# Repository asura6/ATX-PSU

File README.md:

# ATX-PSU
ATX Breakout PCB with current- and voltage monitoring using a STM32 microcontroller and a LCD screen.

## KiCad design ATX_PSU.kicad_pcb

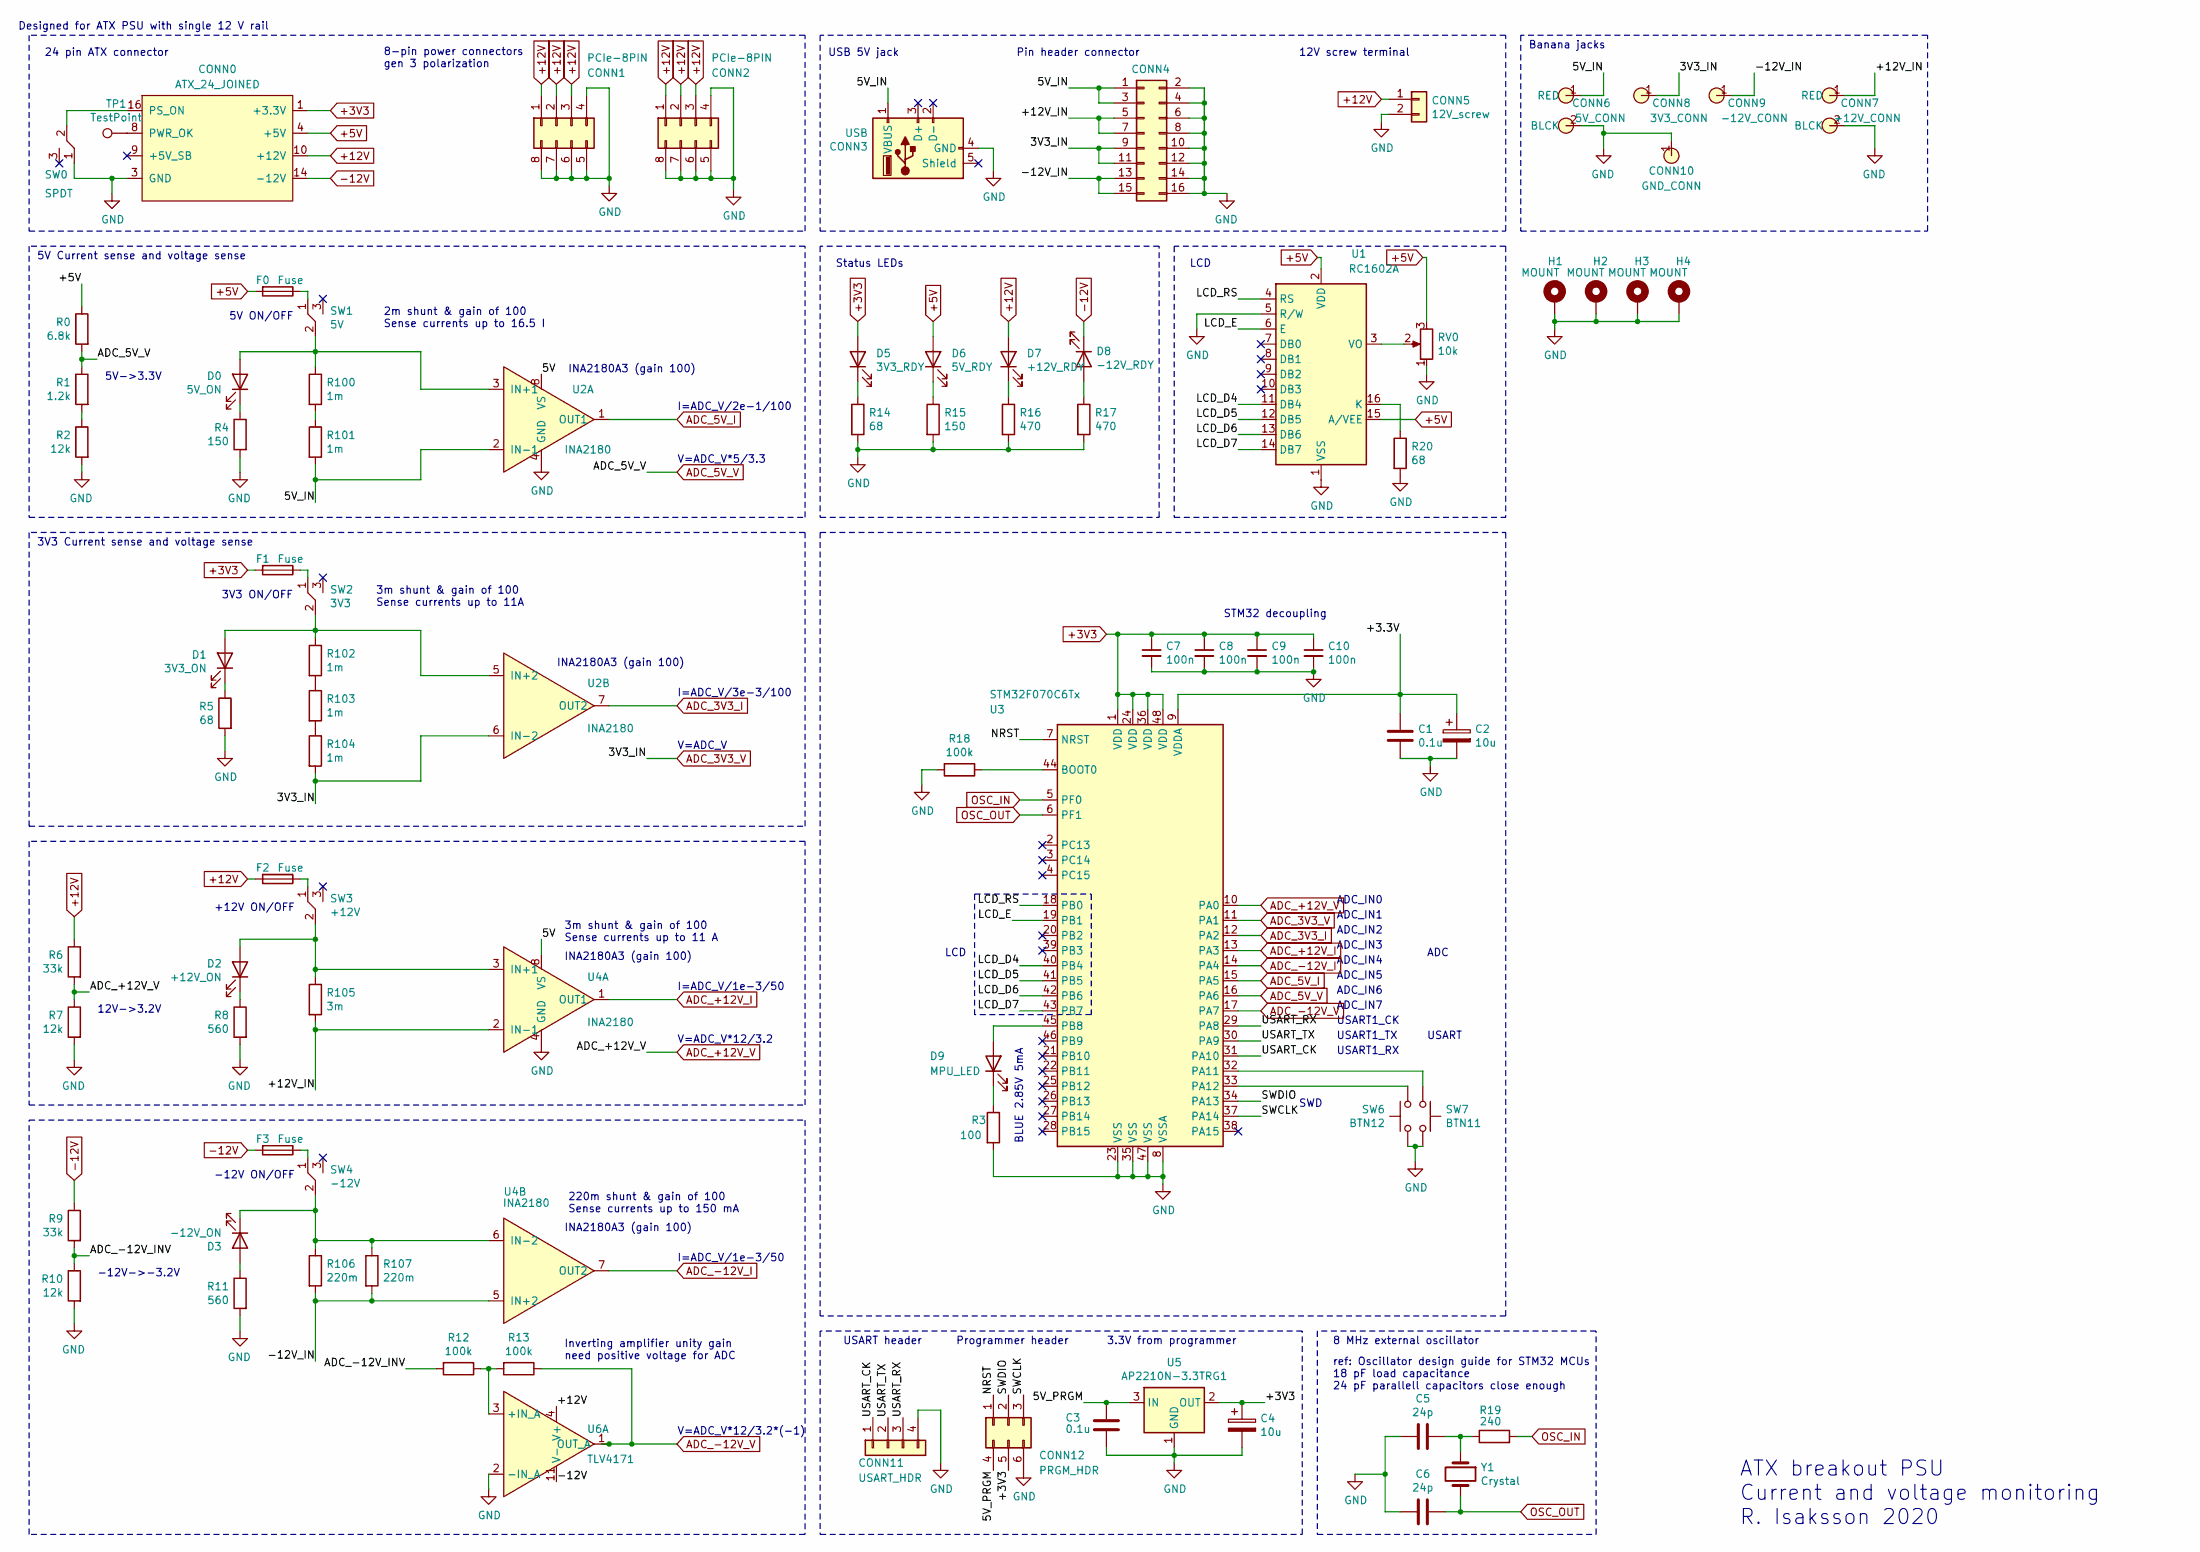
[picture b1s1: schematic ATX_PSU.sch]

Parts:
C1, C3: 0.1u; C_0603_1608Metric
C2, C4: 10u; CP_EIA-3528-12_Kemet-T
C5, C6: 24p; C_0603_1608Metric
C7, C8, C9, C10: 100n; C_0603_1608Metric
CONN0: ATX_24_JOINED; Molex_Mini-Fit_Jr_5569-24A2_2x12_P4.20mm_Horizontal
CONN1, CONN2: PCIe-8PIN; Molex_Mini-Fit_Jr_455860005_2x04_P4.20mm_Horizontal
CONN3: USB; USB_Micro-B_Molex_47346-0001
CONN4: Conn_02x08_Odd_Even; PinHeader_2x08_P2.54mm_Vertical
CONN5: 12V_screw; Phoenix_01x02_1935776
CONN6: 5V_CONN; 2x_BNNA
CONN7: +12V_CONN; 2x_BNNA
CONN8: 3V3_CONN; 1x_BNNA
CONN9: -12V_CONN; 1x_BNNA
CONN10: GND_CONN; 1x_BNNA
CONN11: USART_HDR; PinHeader_1x04_P2.54mm_Vertical
CONN12: PRGM_HDR; PinHeader_2x03_P2.54mm_Vertical
D0: 5V_ON; LED_1206_3216Metric
D1: 3V3_ON; LED_1206_3216Metric
D2: +12V_ON; LED_1206_3216Metric
D3: -12V_ON; LED_1206_3216Metric
D5: 3V3_RDY; LED_1206_3216Metric
D6: 5V_RDY; LED_1206_3216Metric
D7: +12V_RDY; LED_1206_3216Metric
D8: -12V_RDY; LED_1206_3216Metric
D9: MPU_LED; LED_0603_1608Metric
F0, F1, F2, F3: Fuse; Fuseholder_Cylinder-5x20mm_Stelvio-Kontek_PTF78_Horizontal_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
H1, H2, H3, H4: MOUNT; MountingHole_4.3mm_M4_Pad_Via
R0: 6.8k; R_0805_2012Metric
R1: 1.2k; R_0805_2012Metric
R2, R7, R10: 12k; R_0805_2012Metric
R3: 100; R_0805_2012Metric
R4, R15: 150; R_0805_2012Metric
R5, R14, R20: 68; R_0805_2012Metric
R6, R9: 33k; R_0805_2012Metric
R8, R11: 560; R_0805_2012Metric
R12, R13, R18: 100k; R_0805_2012Metric
R16, R17: 470; R_0805_2012Metric
R19: 240; R_0805_2012Metric
R100, R101, R102, R103, R104: 1m; R_2512_6332Metric
R105: 3m; R_1206_3216Metric
R106, R107: 220m; R_1206_3216Metric
RV0: 10k; 3361P
SW0: SPDT; RI_SPDT
SW1: 5V; RI_SPDT
SW2: 3V3; RI_SPDT
SW3: +12V; RI_SPDT
SW4: -12V; RI_SPDT
SW6: BTN12; SW_PUSH_6mm
SW7: BTN11; SW_PUSH_6mm
TP1: TestPoint; TestPoint_THTPad_2.5x2.5mm_Drill1.2mm
U1: RC1602A; LCD_4ROW
U2, U4: INA2180; VSSOP-8_3.0x3.0mm_P0.65mm
U3: STM32F070C6Tx; LQFP-48_7x7mm_P0.5mm
U5: AP2210N-3.3TRG1; SOT-23_Handsoldering
U6: TLV4171; SOIC-14_3.9x8.7mm_P1.27mm
Y1: Crystal; LFXTAL020423

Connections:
+3V3: C4.1, C7.1, C8.1, C9.1, C10.1, CONN0.1 (+3.3V), CONN0.2 (+3.3V), CONN0.12 (+3.3V), CONN0.13 (+3.3V), CONN12.5, D5.2 (A), F1.2, U3.1 (VDD), U3.24 (VDD), U3.36 (VDD), U3.48 (VDD), U5.2 (OUT)
+5V: CONN0.4 (+5V), CONN0.6 (+5V), CONN0.21 (+5V), CONN0.22 (+5V), CONN0.23 (+5V), D6.2 (A), F0.2, R0.1, RV0.3, U1.2 (VDD), U1.15 (A/VEE)
+12V: CONN0.10 (+12V), CONN0.11 (+12V), CONN1.1, CONN1.2, CONN1.3, CONN2.1, CONN2.2, CONN2.3, CONN5.1, D7.2 (A), F2.2, R6.1, U6.4 (V+)
-12V: CONN0.14 (-12V), D8.1 (K), F3.2, R9.1, U6.11 (V-)
/5V: U2.8 (VS), U4.8 (VS)
/5V_IN: CONN3.1 (VBUS), CONN4.1, CONN4.3, CONN6.1 (RED), R101.2, U2.2 (IN-1)
/5V_PRGM: C3.1, CONN12.4, U5.3 (IN)
/+3.3V: C1.1, C2.1, U3.9 (VDDA)
/+12V_IN: CONN4.5, CONN4.7, CONN7.1 (RED), R105.2, U4.2 (IN-1)
/-12V_IN: CONN4.13, CONN4.15, CONN9.1, R106.2, R107.2, U4.5 (IN+2)
/ADC_-12V_INV: R9.2, R10.1, R12.2
/LCD_D4: U1.11 (DB4), U3.40 (PB4)
/LCD_D5: U1.12 (DB5), U3.41 (PB5)
/LCD_D6: U1.13 (DB6), U3.42 (PB6)
/LCD_D7: U1.14 (DB7), U3.43 (PB7)
/LCD_E: U1.6 (E), U3.19 (PB1)
/LCD_RS: U1.4 (RS), U3.18 (PB0)
/NRST: CONN12.1, U3.7 (NRST)
/SWCLK: CONN12.3, U3.37 (PA14)
/SWDIO: CONN12.2, U3.34 (PA13)
/USART_CK: CONN11.1, U3.31 (PA10)
/USART_RX: CONN11.3, U3.29 (PA8)
/USART_TX: CONN11.2, U3.30 (PA9)
ADC_3V3_I: U2.7 (OUT2), U3.12 (PA2)
ADC_3V3_V: CONN4.9, CONN4.11, CONN8.1, R104.2, U2.6 (IN-2), U3.11 (PA1)
ADC_5V_I: U2.1 (OUT1), U3.15 (PA5)
ADC_5V_V: R0.2, R1.1, U3.16 (PA6)
ADC_+12V_I: U3.13 (PA3), U4.1 (OUT1)
ADC_+12V_V: R6.2, R7.1, U3.10 (PA0)
ADC_-12V_I: U3.14 (PA4), U4.7 (OUT2)
ADC_-12V_V: R13.1, U3.17 (PA7), U6.1 (OUT_A)
GND: C1.2, C2.2, C3.2, C4.2, C5.2, C6.2, C7.2, C8.2, C9.2, C10.2, CONN0.3 (GND), CONN0.5 (GND), CONN0.7 (GND), CONN0.15 (GND), CONN0.17 (GND), CONN0.18 (GND), CONN0.19 (GND), CONN0.24 (GND), CONN1.4, CONN1.5, CONN1.6, CONN1.7, CONN1.8, CONN2.4, CONN2.5, CONN2.6, CONN2.7, CONN2.8, CONN3.4 (GND), CONN4.2, CONN4.4, CONN4.6, CONN4.8, CONN4.10, CONN4.12, CONN4.14, CONN4.16, CONN5.2, CONN6.2 (BLCK), CONN7.2 (BLCK), CONN10.1, CONN11.4, CONN12.6, H1.1, H2.1, H3.1, H4.1, R2.2, R3.2, R4.2, R5.2, R7.2, R8.2, R10.2, R11.2, R14.2, R15.2, R16.2, R17.2, R18.2, R20.2, RV0.1, SW0.1, SW6.2, SW7.2, U1.1 (VSS), U1.5 (R/W), U2.4 (GND), U3.8 (VSSA), U3.23 (VSS), U3.35 (VSS), U3.47 (VSS), U4.4 (GND), U5.1 (GND), U6.2 (-IN_A)
unnamed: C5.1, R19.1, Y1.1
unnamed: CONN0.8 (PWR_OK), TP1.1
unnamed: CONN0.16 (PS_ON), SW0.2
unnamed: D0.1 (K), R4.1
unnamed: D0.2 (A), R100.1, SW1.2, U2.3 (IN+1)
unnamed: D1.1 (K), R5.1
unnamed: D1.2 (A), R102.1, SW2.2, U2.5 (IN+2)
unnamed: D2.1 (K), R8.1
unnamed: D2.2 (A), R105.1, SW3.2, U4.3 (IN+1)
unnamed: D3.1 (K), R106.1, R107.1, SW4.2, U4.6 (IN-2)
unnamed: D3.2 (A), R11.1
unnamed: D5.1 (K), R14.1
unnamed: D6.1 (K), R15.1
unnamed: D7.1 (K), R16.1
unnamed: D8.2 (A), R17.1
unnamed: D9.1 (K), R3.1
unnamed: D9.2 (A), U3.45 (PB8)
unnamed: F0.1, SW1.1
unnamed: F1.1, SW2.1
unnamed: F2.1, SW3.1
unnamed: F3.1, SW4.1
unnamed: R1.2, R2.1
unnamed: R12.1, R13.2, U6.3 (+IN_A)
unnamed: R18.1, U3.44 (BOOT0)
unnamed: R20.1, U1.16 (K)
unnamed: R100.2, R101.1
unnamed: R102.2, R103.1
unnamed: R103.2, R104.1
unnamed: RV0.2, U1.3 (VO)
unnamed: SW6.1, U3.33 (PA12)
unnamed: SW7.1, U3.32 (PA11)
OSC_IN: R19.2, U3.5 (PF0)
OSC_OUT: C6.1, U3.6 (PF1), Y1.2

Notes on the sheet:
24 pin ATX connector
Status LEDs
5V Current sense and voltage sense
3m shunt & gain of 100 Sense currents up to 11A
2m shunt & gain of 100 Sense currents up to 16.5 I
USB 5V jack
INA2180A3 (gain 100)
I=ADC_V/3e-3/100
V=ADC_V
I=ADC_V/2e-1/100
5V->3.3V
V=ADC_V*5/3.3
3V3 Current sense and voltage sense
12V->3.2V
V=ADC_V*12/3.2
I=ADC_V/1e-3/50
3m shunt & gain of 100 Sense currents up to 11 A
-12V->-3.2V
V=ADC_V*12/3.2*(-1)
220m shunt & gain of 100 Sense currents up to 150 mA
Inverting amplifier unity gain need positive voltage for ADC
Banana jacks
Pin header connector
Programmer header
8 MHz external oscillator
ref: Oscillator design guide for STM32 MCUs 18 pF load capacitance 24 pF parallell capacitors close enough
3.3V from programmer
ADC_IN0
ADC_IN1
ADC_IN2
ADC_IN3
ADC_IN4
ADC_IN5
ADC_IN6
ADC_IN7
USART1_CK
USART1_TX
USART1_RX
USART header
ADC

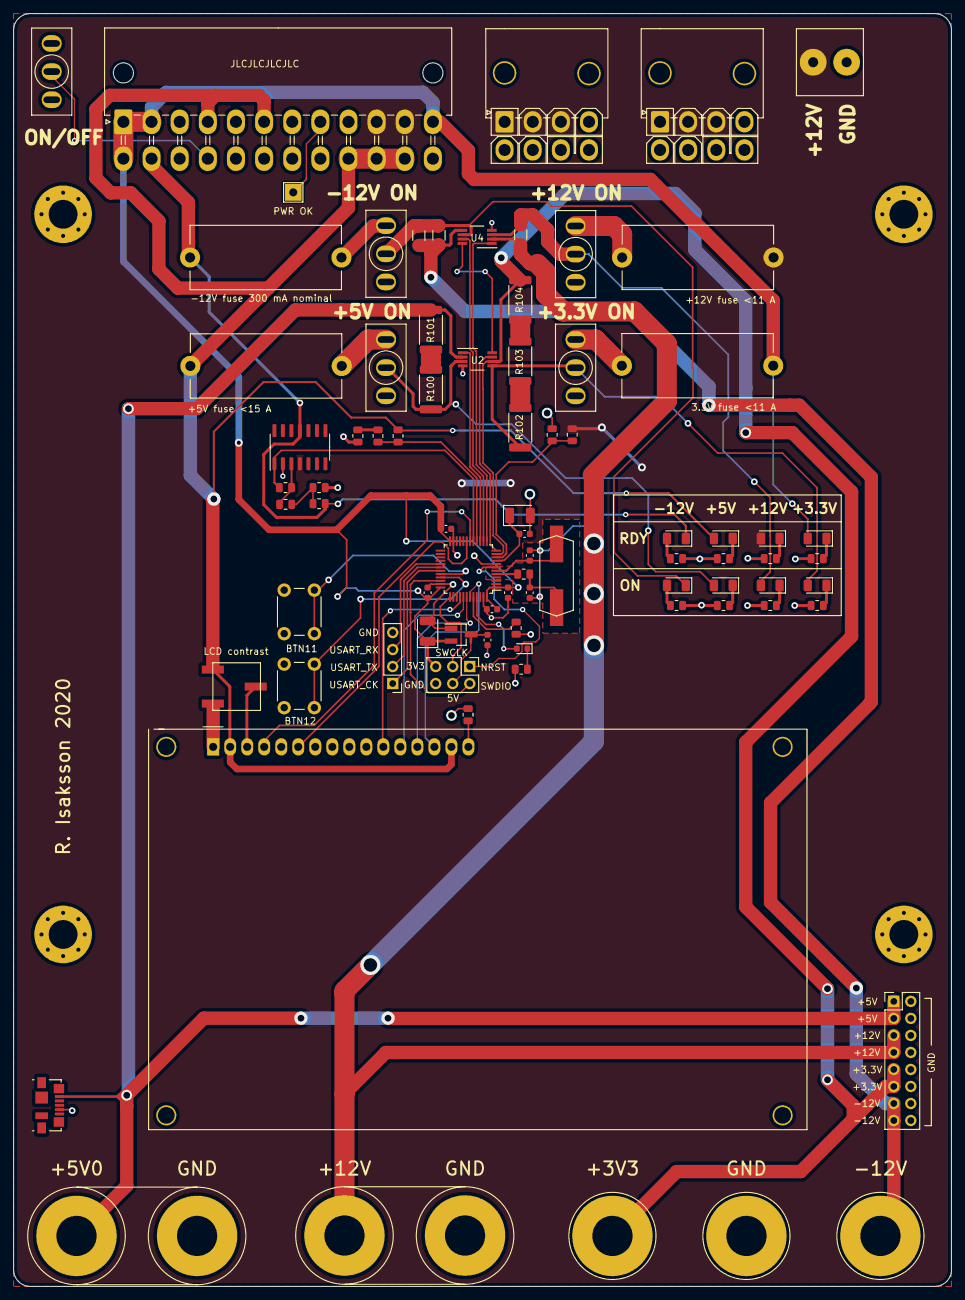
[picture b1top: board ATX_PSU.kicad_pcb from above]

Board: 2 copper layers, 140.0 x 190.0 mm, 85 parts (0 on the bottom side), 65 nets.

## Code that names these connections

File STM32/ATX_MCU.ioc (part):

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Mcu.Name=STM32F070C6Tx
Mcu.Package=LQFP48
Mcu.UserName=STM32F070C6Tx
PA0.Mode=IN0
PA0.Signal=ADC_IN0
PA1.Signal=ADC_IN1
PA10.Mode=Asynchronous
PA10.Signal=USART1_RX
PA11.GPIOParameters=GPIO_PuPd,GPIO_Mode
PA11.GPIO_Mode=GPIO_MODE_INPUT
PA11.GPIO_PuPd=GPIO_NOPULL
PA11.Signal=GPIO_Input
PA12.GPIOParameters=GPIO_PuPd,GPIO_Mode
PA12.GPIO_Mode=GPIO_MODE_INPUT
PA12.GPIO_PuPd=GPIO_NOPULL
PA12.Signal=GPIO_Input
PA13.Mode=Serial_Wire
PA13.Signal=SYS_SWDIO
PA14.Mode=Serial_Wire
PA14.Signal=SYS_SWCLK
PA2.Signal=ADC_IN2
PA3.Signal=ADC_IN3
PA4.Signal=ADC_IN4
PA5.Signal=ADC_IN5
PA6.Signal=ADC_IN6
PA7.Signal=ADC_IN7
PA9.Mode=Asynchronous
PA9.Signal=USART1_TX
PB0.Signal=GPIO_Output
PB1.Signal=GPIO_Output
PB4.Signal=GPIO_Output
PB5.Signal=GPIO_Output
PB6.Signal=GPIO_Output
PB7.Signal=GPIO_Output
PB8.Signal=GPIO_Output
PF0-OSC_IN.Mode=HSE-External-Oscillator
PF0-OSC_IN.Signal=RCC_OSC_IN
PF1-OSC_OUT.Mode=HSE-External-Oscillator
PF1-OSC_OUT.Signal=RCC_OSC_OUT
RCC.SYSCLKFreq_VALUE=48000000
RCC.SYSCLKSource=RCC_SYSCLKSOURCE_PLLCLK
board=custom

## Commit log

2020-11-22 init
2020-11-22 Flash debug scripts (jlink). UART working
2020-11-22 Working on ADC and DMA interrupt
2020-11-23 ADC prototyping
